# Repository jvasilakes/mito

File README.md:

# Mito

A tiny, cheap, hackable, completely open-source force gauge for isometric finger strength training.

## Hardware information

The Mito is based on the Seeed XIAO NRF52840 microcontroller, an HX711 ADC, and a custom load cell. It runs at approximately 80 samples per second on the hardware side, and sends approximately 60 samples per second over bluetooth. Initial tests show a standard error of about 100g. The load cell and two Peguet 3.5mm stainless steel maillon rapides provide a working load limit of 220kg and a breaking load of 1100kg. 

## User Guide

On one side of your device you'll see

 1. A hardware on/off switch
 2. An LED indicator
 3. A tare button

On the other there is a USB-C port that is used for battery charging and firmware updates.

Assuming you've obtained a prebuilt device, it should be ready to go out of the box. Flip the switch to turn it on, and you'll see a green light for 1 second before it changes to yellow. Download the Frez app on your phone, register/sign in to your account, then press the "connect" button on the main page. If the Mito is powered on, a scan of available devices should reveal a device called "Progressor". Connect to it, register it as "Mito" or whatever name you like, and start training!

### Automatic sleep mode

After 1 minute of inactivity (i.e., no weight changes) the Mito will enter sleep mode to save battery. This is indicated by a periodic flashing LED. To wake your Mito up, simply press the tare button and continue your training. After 10 minutes in light sleep, the Mito will enter deep sleep from which it can only be woken up by turning it off and on again.

### Charging the battery

The Mito should need charging very infrequently. The current estimate is at least a few weeks of regular usage before the battery will run low. To charge, plug the Mito into a power source using a USB-C cable and turn it on with the hardware switch. The Mito will enter sleep mode after 1 minute of inactivity and continue to charge, indicated by a longer blinking LED.

### Firmware updates

Firmware updates will be provided here on the Releases page, so keep an eye out. To update your device's firmware with a new version, follow these steps:

 1. Download the new firmware UF2 file onto your computer (e.g., `mito_v0.0.1.uf2`).
 2. Plug your Mito into your computer using the USB-C port while holding down the tare button. Release the button once you see the red light. You've now entered maintenance mode selection.
 3. Use single presses of the tare button to cycle through the maintenance modes until you see a blue light, which indicates firmware update mode. Double click the tare button to select it.
 4. The Mito should turn off and after a few moments a USB device called XIAO-SENSE should pop up on your computer. Simply drag and drop the new UF2 file onto the root folder of this device. Once the copy is complete, the Mito should reset.
 5. Unplug the USB cable and start training!

### Changing the default device mode

The Mito is compatible with the Frez app for visualizing and tracking your training sessions. By default the Mito is in Tindeq mode (yellow light), meaning that it pretends to be a Tindeq device. This mode currently provides the most stable and fastest bluetooth connection to the Frez app. The Tindeq app is currently not supported, and your experience may vary.

If for whatever reason you want your Mito to pretend to be a WH-06 (the original device around which Frez was built), follow these steps:

 1. Turn your Mito on with the hardware switch.
 2. While the initial green light is showing, press the tare button to enter device selection mode. The light should turn blue.
 3. A single press of the tare button will cycle through the available device modes. Blue indicates the WH-06 while yellow indicates the Tindeq.
 4. Press the tare button twice quickly to change the default device to the current selection. The Mito will start up and from now on will be in your chosen device mode every time you turn it on.

If you want to abort this and stay with your current default device, simply turn the Mito off and back on again.

## Known Issues

### Frez Connectivity

It can happen that if you connect your Mito to Frez or another app (e.g., Tindeq), close the app, and the try to reconnect, the initialization will hang and you'll get a device disconnected error. This can be fixed by simply turning the Mito off and on again, and restarting the app.

### Battery Level Indicator

Frez shows battery level next to the connected device icon in the lower right corner. Unfortunately, the battery level sampling on the XIAO microcontroller isn't the most accurate, so you may see inconsistnet values. Overall, however, a low battery indication here is a good sign its time to charge.

## Advanced Usage

### Calibration

All pre-built Mito's are already calibrated. If you need to redo it however, follow these steps:

 1. Download [Serial Bluetooth Terminal](https://play.google.com/store/apps/details?id=de.kai_morich.serial_bluetooth_terminal&pcampaignid=web_share) app on your phone. 
 2. Turn on the Mito while holding down the tare button to enter maintenance mode.
 3. Use single presses of the tare button to cycle through modes until you see a white light. Press the tare button twice quickly to select this, which will enter calibration mode.
 4. Open the Serial Bluetooth Terminal app, scan for devices, and select the Mito.
 5. A terminal window should open. Hang the Mito on something solid, but keep the other anchor free. Once you see `Connecting to Mito... Connected` in the terminal window, send an empty command to start the calibration process. 
 6. After you see `Tared. Enter weight. grams: ` in the terminal, hang a known weight on the free anchor of the Mito. Make sure the weight is stationary and not swinging, twirling, etc.
 7. Enter the weight in grams (e.g., for a 20kg plate you would enter `20000`) and hit send.
 8. The calibration will now run for a few iterations. At the end it will print `Estimated parameter:  Saving...`. 
 9. Power cycle the Mito, connect to the Frez app, and validate that the reading is correct for the weight you used to calibrate. 

### Configuration

You can manually set the following variables in `prototype/src/lib/config.h`. For the changes to take effect, you will need to recompile and upload the firmware to your Mito (see below).

 * `LIGHT_SLEEP_SECONDS`: The number of seconds with no weight changes until the Mito enters light sleep. Default 60.
 * `DEEP_SLEEP_SECONDS`: The number of seconds in light sleep until the Mito enters deep sleep. Default 600.
 * `SCALE_FACTOR`: The calibration scale factor. Default set during calibration (see above). This can be used to fine-tune your precise calibration factor.

### Building the firmware

First, clone this repository or download the code for your chosen release. Then,

```
cd dev
arduino-cli compile --export-binaries --fqbn Seeeduino:nrf52:xiaonRF52840Sense prototype
python ../utils/uf2conv.py prototype/build/Seeeduino.nrf52.xiaonRF52840Sense/prototype.ino.hex --family 0xADA52840 --convert --output prototype/releases/mito_vX.X.X.uf2 
```

Change the `X.X.X` to your desired version. If you've made changes to an official release, I recommend adding a suffix to indicate it (e.g., `mito_v0.0.4_dev.uf2`).

### Debug Mode

If you're doing development and want to access information over serial, plug your Mito into your computer while holding down the tare button. Use single presses of the tare button until you see a red light. Double click the tare button to enter debug mode. In this mode, the Mito will not start its initialization routine until you've connected to it with a serial monitor. 

Once the Mito has begun measuring, it will print data in the following format for each measurement taken from the ADC:

`adc_reading,smoothed_adc_reading,scale_offset,scale_calibration_factor,weight_grams,device_sample_rate_hz,ble_notify_rate_hz,battery_is_charging,battery_voltage,battery_percentage`

It will also print out any commands it receives from the central, and when the device is charging in sleep mode it will print out the current battery percentage.

### Entering firmware update mode with the hardware reset button

It might happen that a failed firmware update means that you can't enter firmware update mode using the method described above. If this happens you'll have to use the hardware reset button on the microcontroller. You can do this in two ways:

 1. Insert a small thin object into the hole below the 'S' on the CRUX TOOLS side of the Mito. a bobby pin works great for this. You'll have to fish around a bit, but the XIAO's reset button should be directly below this. Do your best to double click it. If you're successful, the Mito will turn off and you'll see the XIAO-SENSE USB device pop up on your computer. 
 2. If the above is simply too annoying, you can also open the case using a standard Philip's head screwdriver. If you do this, there is a chance you will have to re-calibrate after putting it together again, since the load cell can get shifted slightly.

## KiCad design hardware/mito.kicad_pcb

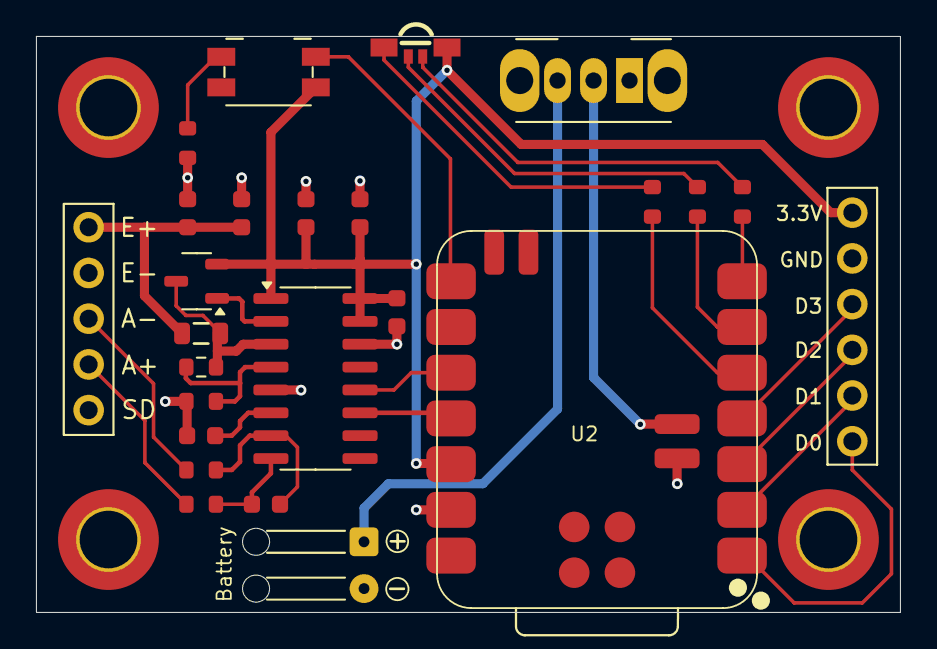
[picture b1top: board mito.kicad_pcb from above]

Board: 2 copper layers, 48.0 x 32.0 mm, 30 parts (0 on the bottom side), 26 nets.

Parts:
C1, C2, C3, C4, C5: 0.1uF; C_0603
C6, C7: 10uF; C_0603
D1: LED_RGBA; LED-SMD_LTST-S310F3WT
FRAME1: FRAME-LETTER; CREATIVE_COMMONS
H1, H2, H3, H4: MountingHole_Pad; MountingHole_3.2mm_M3_DIN965_Pad_TopOnly
J1: Conn_01x02; SolderWire-0.1sqmm_1x02_P3.6mm_D0.4mm_OD1mm_Relief
J2: Conn_01x06; PinHeader_1x06_P2.54mm_Vertical
J5: Conn_01x05; PinHeader_1x05_P2.54mm_Vertical
L1: 3.3uH; L_0805
PWR1: SW_SPDT_321; SW_Slide_SPDT_Angled_CK_OS102011MA1Q
Q1: MMBT4403; SOT-23-3
R1: 12k; R_0603_1608Metric
R2: 8.2K; R_0603
R3, R4: 100; R_0603
R5: 150R; R_0603
R6: 10k; R_0603
R7, R8: 100R; R_0603
TARE1: SW_Push; Panasonic_EVQPUJ_EVQPUA
U1: HX711; SOIC-16_3.9x9.9mm_P1.27mm
U2: XIAO-ESP32-C3-DIP; XIAO-nRF52840-SMD

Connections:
/A+: J5.4, R4.1
/A-: J5.3, R3.1
/AVDD: C3.1, C7.1, J5.1, L1.1
/DAT: U1.12 (DOUT), U2.10 (GPIO9/D9/MISO)
/SCK: U1.11 (PD_SCK), U2.11 (GPIO10/D10/MOSI)
/TARE: R6.1, TARE1.1, U2.8 (GPIO20/D7/RX)
GND: C2.1, C3.2, C4.2, C5.2, C6.2, C7.2, H1.1, H2.1, H3.1, H4.1, J1.2, J2.5, J5.2, J5.5, R2.1, R6.2, U1.5 (AGND), U1.14 (XI), U2.13 (GND), U2.16 (Bat-)
unnamed: D1.3 (BK), R8.1
unnamed: D1.2 (GK), R7.1
unnamed: D1.1 (RK), R5.1
unnamed: J1.1, PWR1.3 (B)
unnamed: J2.1, U2.1 (GPIO2/A0/D0)
unnamed: J2.2, U2.2 (GPIO3/A1/D1)
unnamed: J2.3, U2.3 (GPIO4/A2/D2)
unnamed: J2.4, U2.4 (GPIO5/A3/D3)
unnamed: PWR1.2 (A), U2.15 (Bat+)
unnamed: Q1.1 (B), U1.2 (BASE)
unnamed: L1.2, Q1.3 (C), R1.2, U1.3 (AVDD)
unnamed: C1.2, R4.2, U1.8 (INA+)
unnamed: C1.1, R3.2, U1.7 (INA-)
unnamed: C2.2, U1.6 (VBG)
unnamed: R1.1, R2.2, U1.4 (VFB)
unnamed: R5.2, U2.5 (GPIO6/D4/SDA)
unnamed: R7.2, U2.6 (GPIO7/D5/SCL)
unnamed: R8.2, U2.7 (GPIO21/D6/TX)
VCC: C4.1, C5.1, C6.1, D1.4 (A), J2.6, Q1.2 (E), TARE1.2, U1.1 (VSUP), U1.15 (RATE), U1.16 (DVDD), U2.12 (VCC_3V3)

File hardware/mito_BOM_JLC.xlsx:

reference | quantity | value | footprint | part_number
R1 | 1 | 12k | R_0603 | C22790
R2 | 1 | 8.2K | R_0603 | C309082
R3,R4,R8,R7 | 4.0 | 100R | R_0603 | C25201
R5 | 1 | 180R | R_0603 | C25210
R6 | 1 | 10k | R_0603 | C95204
C1,C2,C3,C4,C5 | 5 | 0.1uF | C_0603 | C24452
C6,C7 | 2 | 10uF | C_1210 | C39232
L1 | 1 | 3.3uH | L_0805 | C51725
Q1 | 1 | MMBT4403 | SOT-23-3 | C8513
U1 | 1 | HX711 | SOIC-16_3.9x9.9mm_P1.27mm | C6705483
D1 | 1 | LED_RGBA | LED-SMD_LTST-S310F3WT | C284951
SW1 | 1 | SW_Push | Panasonic_EVQPUJ_EVQPUA | C128539
PWR | 1 | SW_SPDT_321 | SW_Slide_SPDT_Angled_CK_OS102011MA1Q | C226259

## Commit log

2025-07-12 Add calibration
2025-07-12 Advertisement rate set to ADC rate
2025-07-13 Add filtering
2025-07-14 add hardware
2025-07-25 Allow negative scale parameter
2025-08-02 Add HX711 library to src
2025-08-26 Update prototype
2025-08-26 Upload hardware
2025-08-26 Break out scale methods
2025-08-31 Fix issues with hardware.
2025-08-31 Add enclosure
2025-09-01 Tindeq mode now working
2025-09-01 Breakout xiao pins
2025-09-03 mito V2 pcb
2025-10-02 Update README with PCB image
2025-10-02 Save device code to EEPROM
2025-10-02 Ignore build directory
2025-10-02 Add PCB image
2025-10-02 .txt -> .md
2025-10-02 Fix image
2025-10-13 Tindeq now working
2025-10-13 Update enclosure
2025-10-21 Working prototype
2025-10-27 Calibration over bleuart. Update enclosure.
2025-10-27 bluetooth calibration working properly.
2025-10-27 Correct tindeq timestamps
2025-11-11 Fix casting issue when raw reading is negative.
2025-12-02 Enter DFU via TARE button. No deep sleep in Tindeq mode.
2025-12-02 Small enclosure improvements
2025-12-02 Add utils for creating UF2 releases
2025-12-02 Add pictures
2025-12-03 Add load cell diagram
2025-12-09 Improve connection to Frez and Tindeq
2025-12-09 Update enclosure. Add PCB schematic.
2025-12-09 remove extraneous include
2025-12-09 Tare on measurement start.
2025-12-09 Update debug info
2026-01-06 Scale now notifies at >60Hz in Tindeq mode
2026-01-06 Better alpha values for weight and battery voltage smoothing
2026-01-06 Add some info to debug section
2026-01-06 Add --export-binaries to compile command
2026-01-06 Get started with Mito BLE API
2026-01-06 Be clear about led colors when charging
2026-01-19 Small enclosure update
2026-02-27 Use config.h
2026-02-27 Add eraseFlash
2026-02-27 Change how device name is set
2026-03-01 Minor formatting and comments.
2026-03-01 More sane directory structure
2026-03-01 Fix links to images
2026-03-01 Add link to bluetooth serial terminal app

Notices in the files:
parts and their libraries:
Released under the Creative Commons Attribution Share-Alike 4.0 License
https://creativecommons.org/licenses/by-sa/4.0
